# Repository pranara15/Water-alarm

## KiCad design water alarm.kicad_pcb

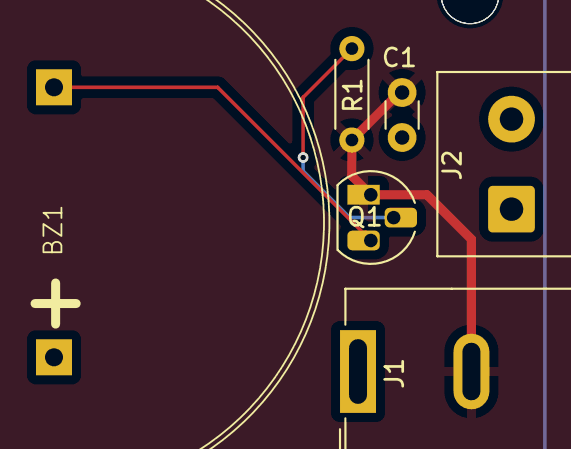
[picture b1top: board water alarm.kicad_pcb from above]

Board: 2 copper layers, 6 parts (0 on the bottom side), 4 nets.

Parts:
BZ1: BUZZER; Buzzer_D30mm_H20mm_P15mm__668-1652-ND__AI-3035-TT-12V-R
C1: 1nF; C_Disc_D3.0mm_W1.6mm_P2.50mm
J1: Jack-DC; BarrelJack_GCT_DCJ200-10-A_Horizontal
J2: Screw_Terminal_01x02; TerminalBlock_Phoenix_PT-1,5-2-5.0-H_1x02_P5.00mm_Horizontal
Q1: 2N7000; TO-92L_HandSolder
R1: 10M; R_Axial_DIN0204_L3.6mm_D1.6mm_P5.08mm_Horizontal

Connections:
/Gate: C1.1, J2.2, Q1.2 (G), R1.1
GND: C1.2, J1.2, Q1.1 (S), R1.2
unnamed: BZ1.2 (-), Q1.3 (D)
VCC: BZ1.1 (+), J1.1, J2.1
